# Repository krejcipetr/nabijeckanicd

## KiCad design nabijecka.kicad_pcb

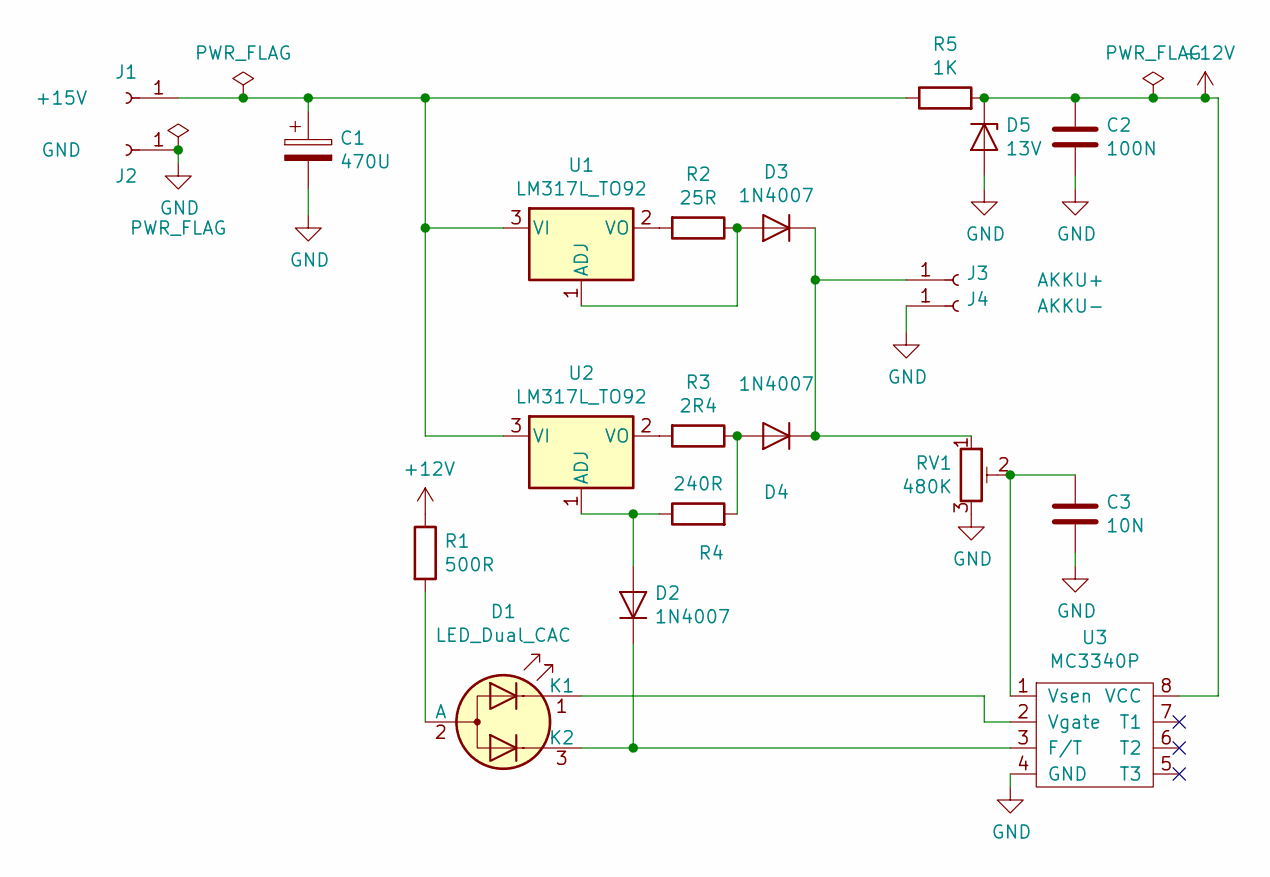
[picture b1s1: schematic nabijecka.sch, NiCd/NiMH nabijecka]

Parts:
C1: 470U; CP_Radial_D8.0mm_P3.50mm
C2: 100N; C_Rect_L7.2mm_W2.5mm_P5.00mm_FKS2_FKP2_MKS2_MKP2
C3: 10N; C_Rect_L7.2mm_W2.5mm_P5.00mm_FKS2_FKP2_MKS2_MKP2
D1: LED_Dual_CAC; LED_D5.0mm-3
D2, D3, D4: 1N4007; D_DO-41_SOD81_P10.16mm_Horizontal
D5: 13V; D_DO-41_SOD81_P10.16mm_Horizontal
J1: +15V; Pin_D1.4mm_L8.5mm_W2.8mm_FlatFork
J2: GND; Pin_D1.4mm_L8.5mm_W2.8mm_FlatFork
J3: AKKU+; Pin_D1.4mm_L8.5mm_W2.8mm_FlatFork
J4: AKKU-; Pin_D1.4mm_L8.5mm_W2.8mm_FlatFork
R1: 500R; R_Axial_DIN0309_L9.0mm_D3.2mm_P12.70mm_Horizontal
R2: 25R; R_Axial_DIN0309_L9.0mm_D3.2mm_P12.70mm_Horizontal
R3: 2R4; R_Axial_DIN0309_L9.0mm_D3.2mm_P25.40mm_Horizontal
R4: 240R; R_Axial_DIN0309_L9.0mm_D3.2mm_P12.70mm_Horizontal
R5: 1K; R_Axial_DIN0309_L9.0mm_D3.2mm_P12.70mm_Horizontal
RV1: 480K; Potentiometer_Piher_PT-10-V10_Vertical_Hole
U1, U2: LM317L_TO92; TO-220-3_Vertical
U3: MC3340P; DIP-8_W7.62mm

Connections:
+12V: C2.1, D5.1 (K), R1.1, R5.2, U3.8 (VCC)
GND: C1.2, C2.2, C3.2, D5.2 (A), J2.1, J4.1, RV1.3, U3.4 (GND); also elsewhere on the board
unnamed 2: C1.1, J1.1, R5.1, U1.3 (VI), U2.3 (VI); also elsewhere on the board
unnamed: C3.1, RV1.2, U3.1 (Vsen)
unnamed: D1.1 (K1), U3.2 (Vgate)
unnamed: D1.2 (A), R1.2
unnamed: D1.3 (K2), D2.1 (K), U3.3 (F/T)
unnamed: D2.2 (A), R4.1, U2.1 (ADJ)
unnamed: D3.1 (K), D4.1 (K), J3.1, RV1.1
unnamed: D3.2 (A), R2.1, U1.1 (ADJ)
unnamed: D4.2 (A), R3.1, R4.2
unnamed: R2.2, U1.2 (VO)
unnamed: R3.2, U2.2 (VO)

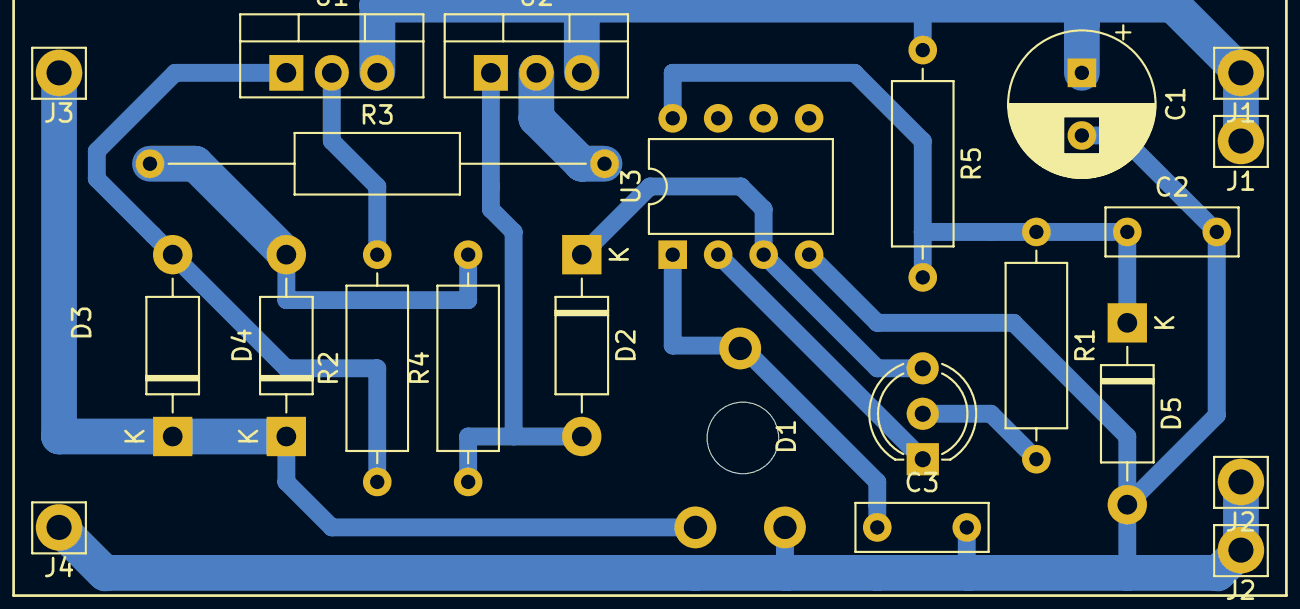
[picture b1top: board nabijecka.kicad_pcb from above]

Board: 2 copper layers, 23 parts (1 on the bottom side), 13 nets.

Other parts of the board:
J1#2: +15V; Pin_D1.4mm_L8.5mm_W2.8mm_FlatFork
J2#2: GND; Pin_D1.4mm_L8.5mm_W2.8mm_FlatFork

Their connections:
GND: J2#2.1; also elsewhere on the board
unnamed 2: J1#2.1; also elsewhere on the board
